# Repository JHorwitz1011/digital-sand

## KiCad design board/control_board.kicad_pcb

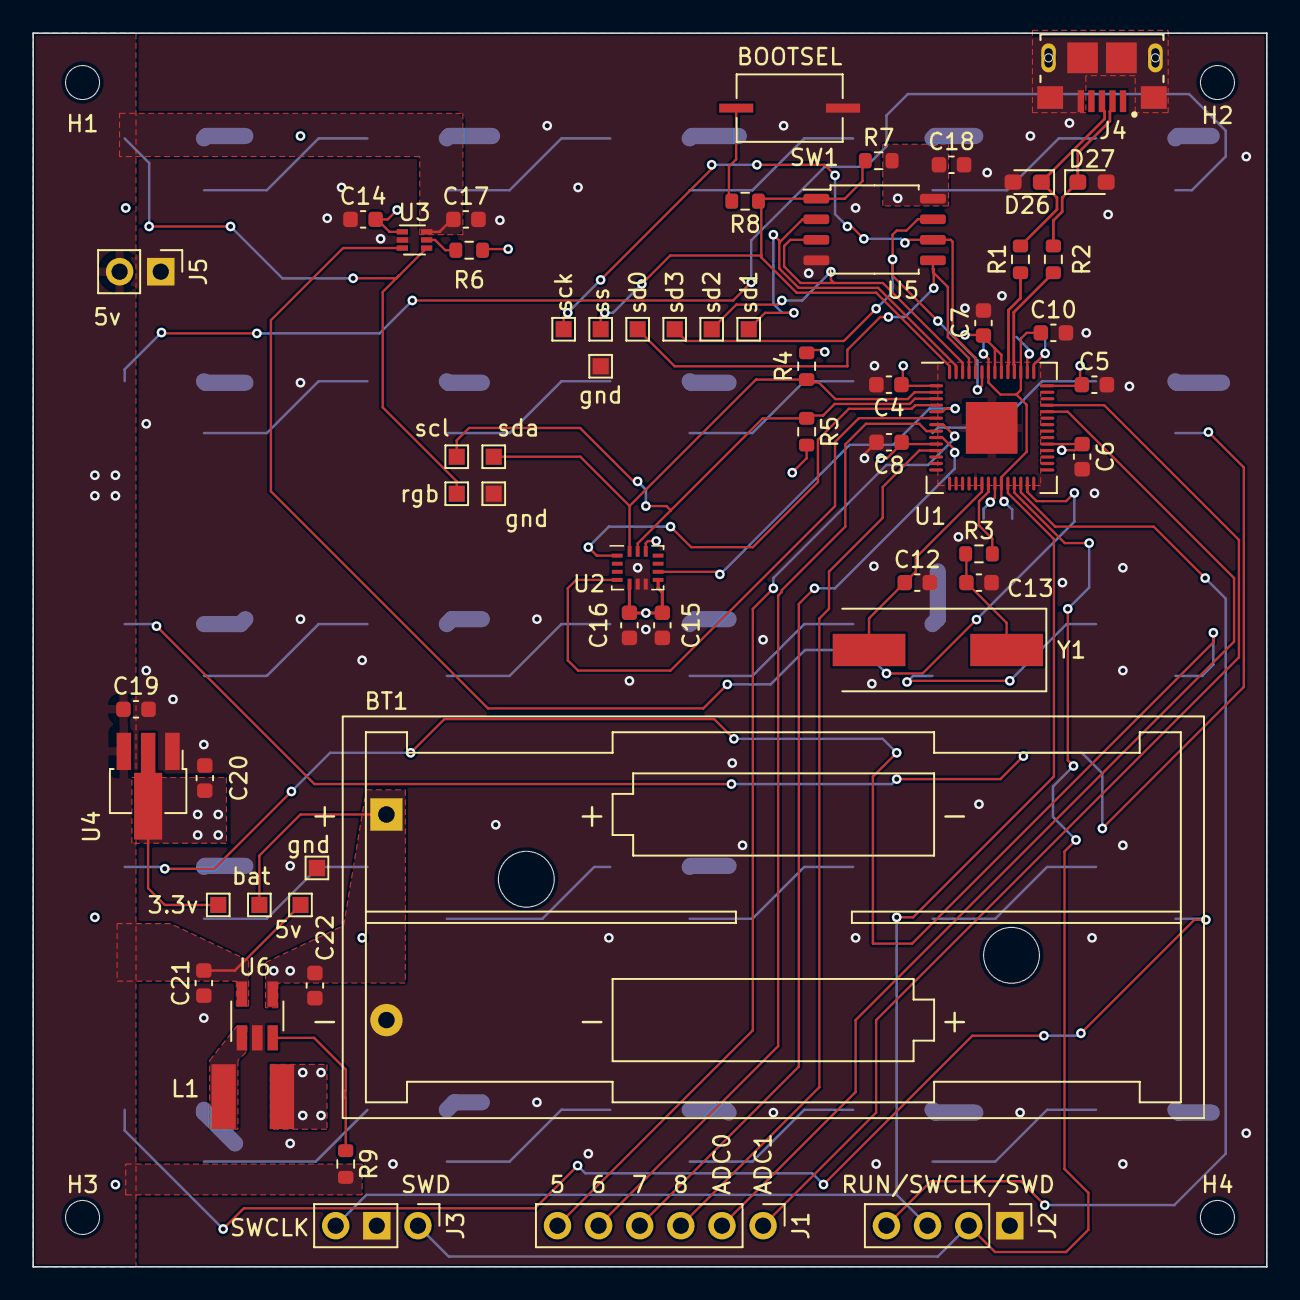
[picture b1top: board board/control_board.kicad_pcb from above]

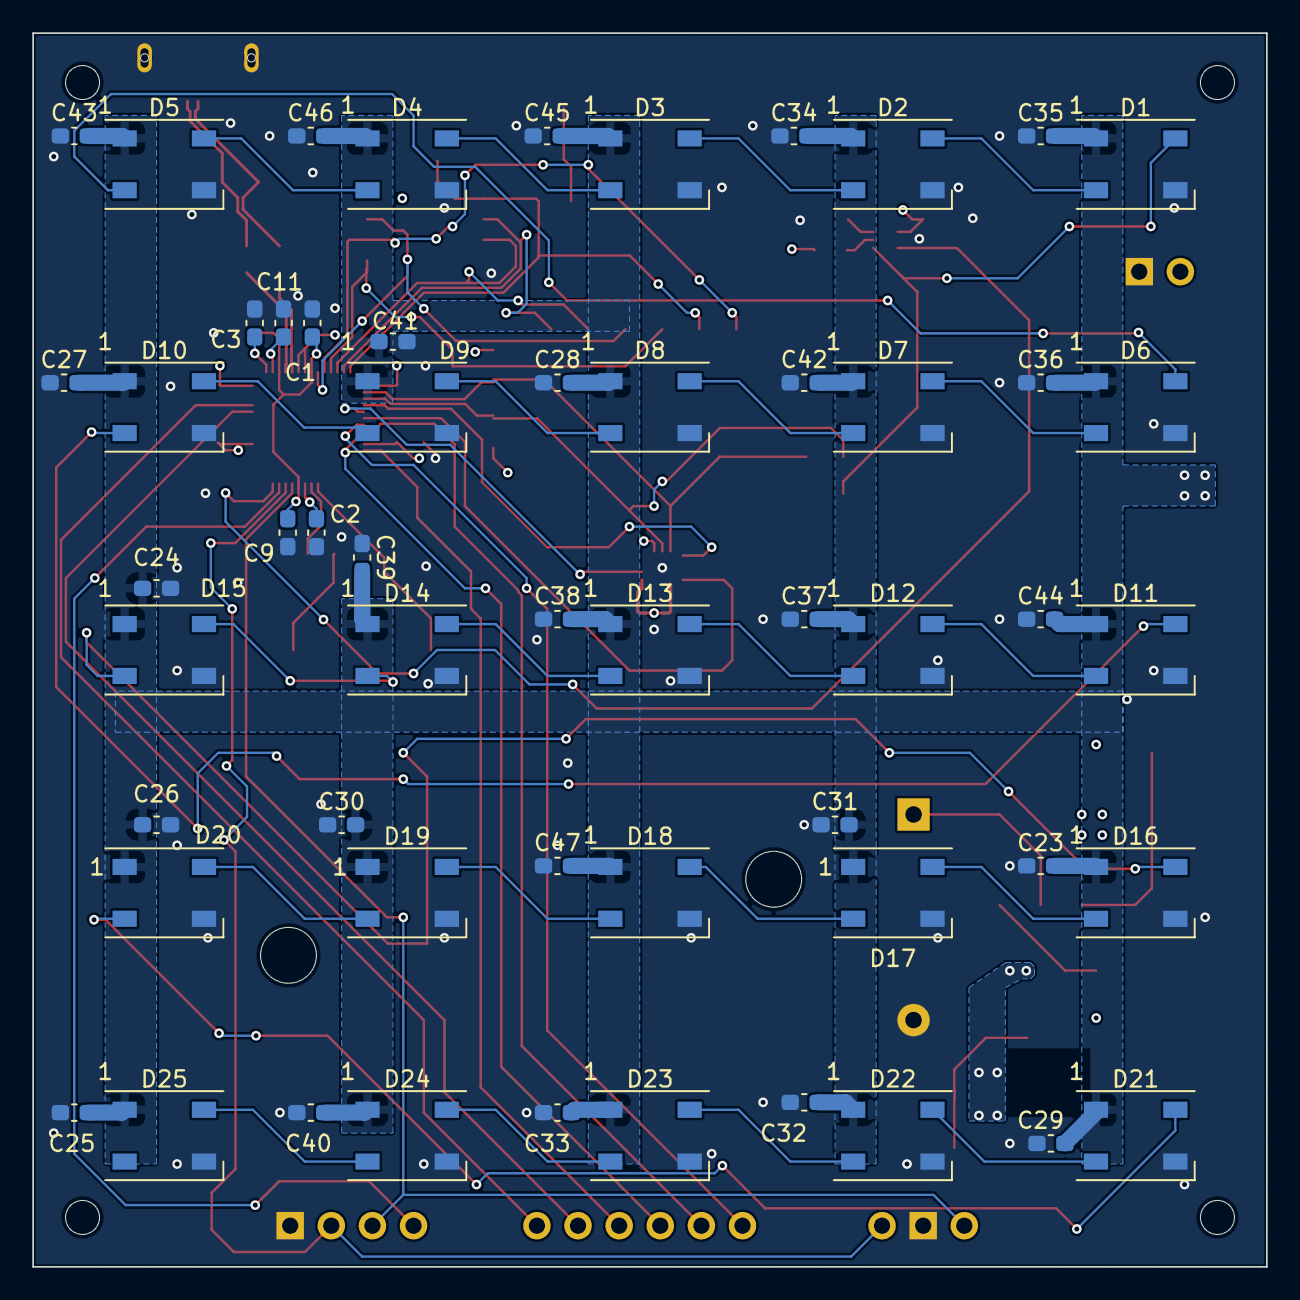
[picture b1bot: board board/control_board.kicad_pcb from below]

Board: 4 copper layers, 76.2 x 76.2 mm, 117 parts (55 on the bottom side), 62 nets.

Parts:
3.3v, 5v: TestPoint; TestPoint_Pad_1.0x1.0mm
BT1: PRT13851; BatteryHolder_Keystone_2468_2xAAA
C1, C2, C3, C9: 100n; C_0603_1608Metric_Pad1.08x0.95mm_HandSolder
C4, C5, C6, C7, C8: 100n; C_0603_1608Metric
C10: 1u; C_0603_1608Metric
C11: 1u; C_0603_1608Metric_Pad1.08x0.95mm_HandSolder
C12, C13: 27p; C_0603_1608Metric
C14, C17: 0.1u; C_0603_1608Metric
C15, C16: 100nF; C_0603_1608Metric
C18, C19, C20: 10u; C_0603_1608Metric
C21, C22: 10uF; C_0603_1608Metric
C23, C24, C25, C26, C27, C28, C29, C30, C31, C32, C33, C34, C35, C36, C37, C38, C39, C40, C41, C42, C43, C44, C45, C46, C47: .1uF; C_0603_1608Metric_Pad1.08x0.95mm_HandSolder
D1, D2, D3, D4, D5, D6, D7, D8, D9, D10, D11, D12, D13, D14, D15, D16, D17, D18, D19, D20, D21, D22, D23, D24, D25: WS2812B; LED_WS2812B_PLCC4_5.0x5.0mm_P3.2mm
D26, D27: D; D_0603_1608Metric_Pad1.05x0.95mm_HandSolder
H1, H2, H3, H4: MountingHole; MountingHole_2.1mm
J1: Conn_01x06; PinHeader_1x06_P2.54mm_Vertical
J2: Conn_01x04; PinHeader_1x04_P2.54mm_Vertical
J3: SWD; PinHeader_1x03_P2.54mm_Vertical
J4: USB_B_Micro; Amphenol_MicroB_10118193
J5: Conn_01x02; PinHeader_1x02_P2.54mm_Vertical
L1: 2.2uH; Inductor_NRS5024T2R2NMGJ
R1, R2: 27.4; R_0603_1608Metric
R3, R8: 1k; R_0603_1608Metric
R4, R5, R6, R7, R9: 10k; R_0603_1608Metric
SW1: BOOTSEL; PTS636 6.0x3.5 Button
U1: RP2040; QFN-56_EP_7.75x7.75_Pitch0.4mm
U2: BMI270; Bosch_LGA-14_3x2.5mm_P0.5mm
U3: SN74LVC1T45DRL; SOT-563
U4: AZ1117-3.3; SOT-89-3_Handsoldering
U5: W25Q128JVS; SOIC-8_5.23x5.23mm_P1.27mm
U6: RP402N; SOT-23-5_HandSoldering
Y1: Crystal; Crystal_SMD_HC49-SD
bat: TestPoint; TestPoint_Pad_1.0x1.0mm
gnd: TestPoint; TestPoint_Pad_1.0x1.0mm
gnd#2, gnd#3: TestPoint; TestPoint_Pad_1.0x1.0mm
rgb: TestPoint; TestPoint_Pad_1.0x1.0mm
sck: TestPoint; TestPoint_Pad_1.0x1.0mm
scl: TestPoint; TestPoint_Pad_1.0x1.0mm
sd0, sd1, sd2, sd3: TestPoint; TestPoint_Pad_1.0x1.0mm
sda: TestPoint; TestPoint_Pad_1.0x1.0mm
ss: TestPoint; TestPoint_Pad_1.0x1.0mm

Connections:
+1V1: C1.1, C2.1, C10.1, U1.23 (DVDD), U1.45 (VREG_VOUT), U1.50 (DVDD)
+3V3: 3.3v.1, C3.1, C4.1, C5.1, C6.1, C7.1, C8.1, C9.1, C11.1, C14.2, C15.2, C16.1, C18.1, C20.1, R4.2, R5.2, R6.2, R7.2, U1.1 (IOVDD), U1.10 (IOVDD), U1.22 (IOVDD), U1.33 (IOVDD), U1.42 (IOVDD), U1.43 (ADC_IOVDD), U1.44 (VREG_IOVDD), U1.48 (USB_IOVDD), U1.49 (IOVDD), U2.5 (VDDIO), U2.8 (VDD), U2.12 (CSB), U3.1 (VCCA), U4.2 (VO), U5.8 (VCC)
+5V: 5v.1, C17.1, C19.1, C21.2, C23.2, C24.2, C25.2, C26.2, C27.2, C28.2, C29.2, C30.2, C31.2, C32.2, C33.2, C34.2, C35.2, C36.2, C37.2, C38.2, C39.2, C40.2, C41.2, C42.2, C43.2, C44.2, C45.2, C46.2, C47.2, D1.1 (VDD), D2.1 (VDD), D3.1 (VDD), D4.1 (VDD), D5.1 (VDD), D6.1 (VDD), D7.1 (VDD), D8.1 (VDD), D9.1 (VDD), D10.1 (VDD), D11.1 (VDD), D12.1 (VDD), D13.1 (VDD), D14.1 (VDD), D15.1 (VDD), D16.1 (VDD), D17.1 (VDD), D18.1 (VDD), D19.1 (VDD), D20.1 (VDD), D21.1 (VDD), D22.1 (VDD), D23.1 (VDD), D24.1 (VDD), D25.1 (VDD), J5.2, R9.2, U3.6 (VCCB), U4.3 (VI), U6.5 (VOUT)
+BATT: BT1.1 (+), C22.2, L1.1, U6.4 (VIN), bat.1
/ADC0: J1.2, U1.38 (GPIO26_ADC0)
/ADC1: J1.1, U1.39 (GPIO27_ADC1)
/CRYSTAL_OUT: C13.1, R3.1, Y1.1
/GPIO5: J1.6, U1.7 (GPIO5)
/GPIO6: J1.5, U1.8 (GPIO6)
/GPIO7: J1.4, U1.9 (GPIO7)
/GPIO8: J1.3, U1.11 (GPIO8)
/IMU INT1: U1.6 (GPIO4), U2.4 (INT1)
/IMU INT2: U1.5 (GPIO3), U2.9 (INT2)
/Lx: L1.2, U6.1 (Lx)
/NEOPIX: U1.27 (GPIO16), U3.3 (A)
/QSPI_SCLK: U1.52 (QSPI_SCLK), U5.6 (CLK), sck.1
/QSPI_SD0: U1.53 (QSPI_SD0), U5.5 (DI(IO0)), sd0.1
/QSPI_SD1: U1.55 (QSPI_SD1), U5.2 (DO(IO1)), sd1.1
/QSPI_SD2: U1.54 (QSPI_SD2), U5.3 (IO2), sd2.1
/QSPI_SD3: U1.51 (QSPI_SD3), U5.7 (IO3), sd3.1
/QSPI_SS: R7.1, R8.1, U1.56 (QSPI_SS), U5.1 (~CS), ss.1
/RGB_DIN: D1.4 (DIN), U3.4 (B), rgb.1
/RPN: R2.1, U1.46 (USB_DM)
/RPP: R1.1, U1.47 (USB_DP)
/RUN: J2.4, U1.26 (RUN)
/SA0: U1.4 (GPIO2), U2.1 (SDO)
/SCL: R5.1, U1.3 (GPIO1), U2.13 (SCx), scl.1
/SDA: R4.1, U1.2 (GPIO0), U2.14 (SDx), sda.1
/SWCLK: J2.3, J3.3, U1.24 (SWCLK)
/SWD: J2.2, J3.1, U1.25 (SWD)
/USB_BOOT: R8.2, SW1.2
/USB_DN: D27.1 (K), J4.2 (D-), R2.2
/USB_DP: D26.1 (K), J4.3 (D+), R1.2
/XIN: C12.1, U1.20 (XIN), Y1.2
/XOUT: R3.2, U1.21 (XOUT)
GND: BT1.2 (-), C1.2, C2.2, C3.2, C4.2, C5.2, C6.2, C7.2, C8.2, C9.2, C10.2, C11.2, C12.2, C13.2, C14.1, C15.1, C16.2, C17.2, C18.2, C19.2, C20.2, C21.1, C22.1, C23.1, C24.1, C25.1, C26.1, C27.1, C28.1, C29.1, C30.1, C31.1, C32.1, C33.1, C34.1, C35.1, C36.1, C37.1, C38.1, C39.1, C40.1, C41.1, C42.1, C43.1, C44.1, C45.1, C46.1, C47.1, D1.3 (VSS), D2.3 (VSS), D3.3 (VSS), D4.3 (VSS), D5.3 (VSS), D6.3 (VSS), D7.3 (VSS), D8.3 (VSS), D9.3 (VSS), D10.3 (VSS), D11.3 (VSS), D12.3 (VSS), D13.3 (VSS), D14.3 (VSS), D15.3 (VSS), D16.3 (VSS), D17.3 (VSS), D18.3 (VSS), D19.3 (VSS), D20.3 (VSS), D21.3 (VSS), D22.3 (VSS), D23.3 (VSS), D24.3 (VSS), D25.3 (VSS), D26.2 (A), D27.2 (A), J2.1, J3.2, J4.5 (GND), J4.6 (Shield), J5.1, SW1.1, U1.19 (TESTEN), U1.57 (GND), U2.6 (GNDIO), U2.7 (GND), U3.2 (GND), U4.1 (GND), U5.4 (GND), U6.2 (GND), gnd.1, gnd#2.1, gnd#3.1
unnamed: D1.2 (DOUT), D2.4 (DIN)
unnamed: D2.2 (DOUT), D3.4 (DIN)
unnamed: D3.2 (DOUT), D4.4 (DIN)
unnamed: D4.2 (DOUT), D5.4 (DIN)
unnamed: D5.2 (DOUT), D6.4 (DIN)
unnamed: D6.2 (DOUT), D7.4 (DIN)
unnamed: D7.2 (DOUT), D8.4 (DIN)
unnamed: D8.2 (DOUT), D9.4 (DIN)
unnamed: D10.2 (DOUT), D11.4 (DIN)
unnamed: D9.2 (DOUT), D10.4 (DIN)
unnamed: D11.2 (DOUT), D12.4 (DIN)
unnamed: D12.2 (DOUT), D13.4 (DIN)
unnamed: D13.2 (DOUT), D14.4 (DIN)
unnamed: D14.2 (DOUT), D15.4 (DIN)
unnamed: D15.2 (DOUT), D16.4 (DIN)
unnamed: D16.2 (DOUT), D17.4 (DIN)
unnamed: D17.2 (DOUT), D18.4 (DIN)
unnamed: D18.2 (DOUT), D19.4 (DIN)
unnamed: D19.2 (DOUT), D20.4 (DIN)
unnamed: D20.2 (DOUT), D21.4 (DIN)
unnamed: D21.2 (DOUT), D22.4 (DIN)
unnamed: D22.2 (DOUT), D23.4 (DIN)
unnamed: D23.2 (DOUT), D24.4 (DIN)
unnamed: D24.2 (DOUT), D25.4 (DIN)
unnamed: R6.1, U3.5 (DIR)
unnamed: R9.1, U6.3 (EN)

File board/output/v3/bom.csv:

Comment,Designator,Footprint,LCSC Part #
100n Unpolarized capacitor,"C1,C2,C3,C9",C_0603_1608Metric_Pad1.08x0.95mm_HandSolder,
100n Unpolarized capacitor,"C4,C5,C6,C7,C8",C_0603_1608Metric,
1u Unpolarized capacitor,C10,C_0603_1608Metric,
1u Unpolarized capacitor,C11,C_0603_1608Metric_Pad1.08x0.95mm_HandSolder,
27p Unpolarized capacitor,"C12,C13",C_0603_1608Metric,
0.1u Unpolarized capacitor,"C14,C17",C_0603_1608Metric,
100nF Unpolarized capacitor,"C15,C16",C_0603_1608Metric,
10u Unpolarized capacitor,"C18,C19,C20",C_0603_1608Metric,
10uF Unpolarized capacitor,"C21,C22",C_0603_1608Metric,
.1uF Unpolarized capacitor,"C23,C24,C25,C26,C27,C28,C29,C30,C31,C32,C33,C34,C35,C36,C37,C38,C39,C40,C41,C42,C43,C44,C45,C46,C47",C_0603_1608Metric_Pad1.08x0.95mm_HandSolder,
WS2812B RGB LED with integrated controller,"D1,D2,D3,D4,D5,D6,D7,D8,D9,D10,D11,D12,D13,D14,D15,D16,D17,D18,D19,D20,D21,D22,D23,D24,D25",LED_WS2812B_PLCC4_5.0x5.0mm_P3.2mm,C2761795
D Diode,"D26,D27",D_0603_1608Metric_Pad1.05x0.95mm_HandSolder,C5224062
USB_B_Micro USB Micro Type B connector,J4,Amphenol_MicroB_10118193,C132562
2.2uH Inductor,L1,Inductor_NRS5024T2R2NMGJ,C222926
27.4 Resistor,"R1,R2",R_0603_1608Metric,
1k Resistor,"R3,R8",R_0603_1608Metric,
10k Resistor,"R4,R5,R6,R7,R9",R_0603_1608Metric,
"BOOTSEL 1x DIP Switch, Single Pole Single Throw (SPST) switch, small symbol",SW1,PTS636 6.0x3.5 Button,C2800965
RP2040 ,U1,QFN-56_EP_7.75x7.75_Pitch0.4mm,C2040
BMI270 ,U2,Bosch_LGA-14_3x2.5mm_P0.5mm,C2836813
"SN74LVC1T45DRL Single-Bit Dual-Supply Bus Transceiver With Configurable Voltage Translation and 3-State Outputs, SOT-563",U3,SOT-563,C352970
"AZ1117-3.3 1A 20V Fixed LDO Linear Regulator, 3.3V, SOT-89/SOT-223/TO-220/TO-252/TO-263",U4,SOT-89-3_Handsoldering,C460428
"W25Q128JVS 128Mb Serial Flash Memory, Standard/Dual/Quad SPI, SOIC-8",U5,SOIC-8_5.23x5.23mm_P1.27mm,C2613930
Crystal Two pin crystal,Y1,Crystal_SMD_HC49-SD,C1985239

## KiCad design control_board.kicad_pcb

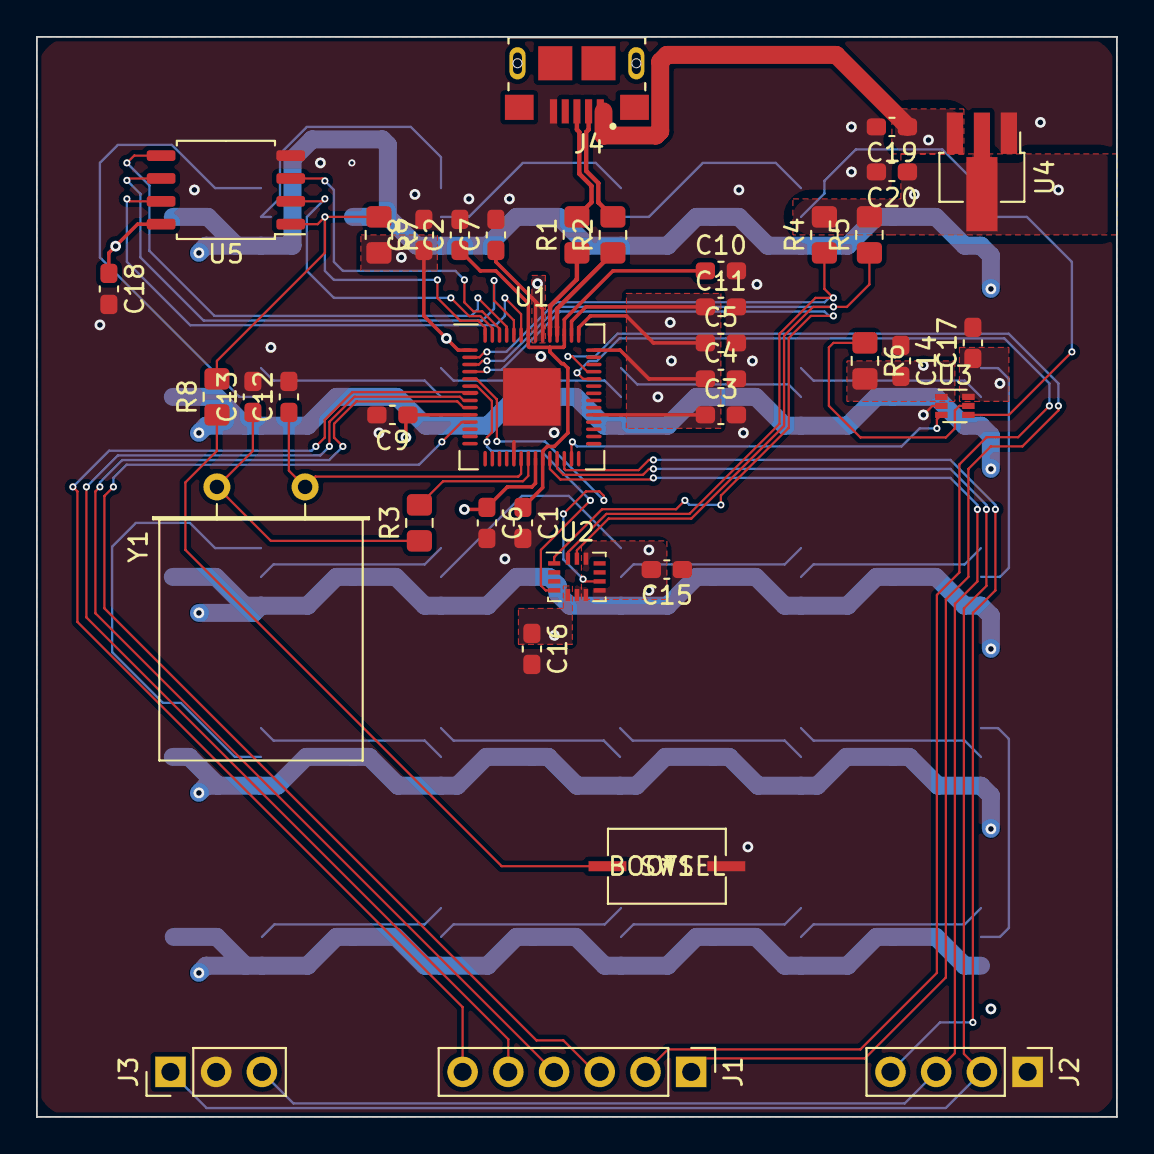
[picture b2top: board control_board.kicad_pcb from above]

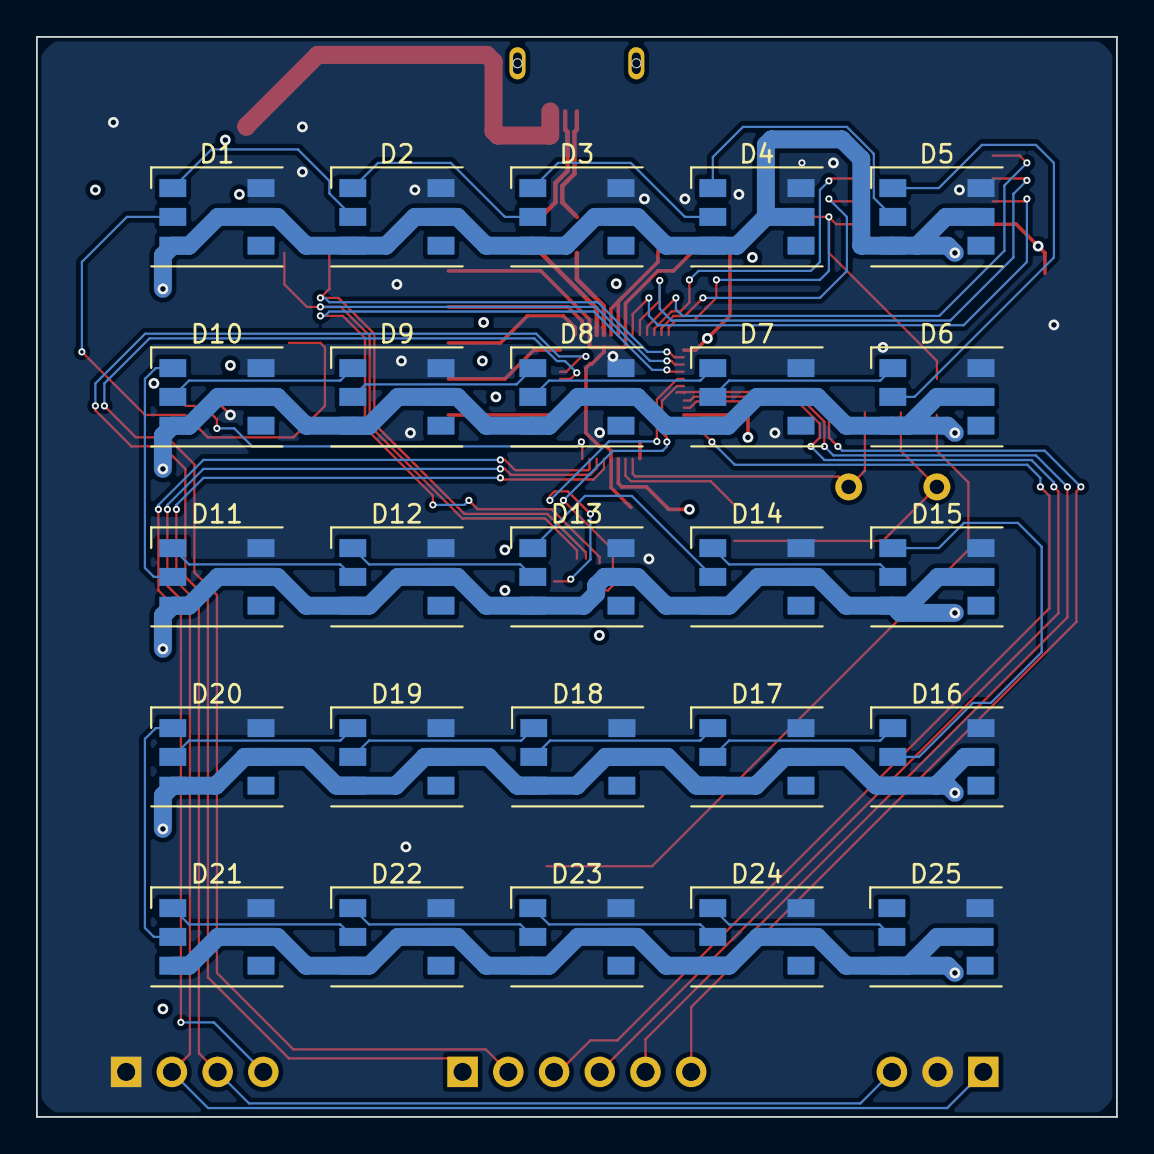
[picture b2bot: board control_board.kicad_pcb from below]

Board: 4 copper layers, 60.0 x 60.0 mm, 64 parts (25 on the bottom side), 59 nets.

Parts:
C1, C2, C3, C4, C5, C6, C7, C8, C9: 100n; C_0603_1608Metric_Pad1.08x0.95mm_HandSolder
C10, C11: 1u; C_0603_1608Metric_Pad1.08x0.95mm_HandSolder
C12, C13: 27p; C_0603_1608Metric_Pad1.08x0.95mm_HandSolder
C14, C17: 0.1u; C_0603_1608Metric_Pad1.08x0.95mm_HandSolder
C15, C16: 100nF; C_0603_1608Metric_Pad1.08x0.95mm_HandSolder
C18, C19, C20: 10u; C_0603_1608Metric_Pad1.08x0.95mm_HandSolder
D1, D2, D3, D4, D5, D6, D7, D8, D9, D10, D11, D12, D13, D14, D15, D16, D17, D18, D19, D20, D21, D22, D23, D24, D25: WS2812; LED_WS2812_PLCC6_5.0x5.0mm_P1.6mm
J1: Conn_01x06; PinHeader_1x06_P2.54mm_Vertical
J2: Conn_01x04; PinHeader_1x04_P2.54mm_Vertical
J3: SWD; PinHeader_1x03_P2.54mm_Vertical
J4: USB_B_Micro; Amphenol_MicroB_10118193
R1, R2: 27.4; R_0805_2012Metric_Pad1.20x1.40mm_HandSolder
R3, R8: 1k; R_0805_2012Metric_Pad1.20x1.40mm_HandSolder
R4, R5, R6, R7: 10k; R_0805_2012Metric_Pad1.20x1.40mm_HandSolder
SW1: BOOTSEL; PTS636 SM25F SMTR LFS
U1: RP2040; QFN-56_EP_7.75x7.75_Pitch0.4mm
U2: BMI270; Bosch_LGA-14_3x2.5mm_P0.5mm
U3: SN74LVC1T45DRL; SOT-563
U4: AZ1117-3.3; SOT-89-3_Handsoldering
U5: W25Q128JVS; SOIC-8_5.23x5.23mm_P1.27mm
Y1: Crystal; Crystal_HC49-U_Horizontal

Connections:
+1V1: C1.1, C2.1, C10.1, U1.23 (DVDD), U1.45 (VREG_VOUT), U1.50 (DVDD)
+3V3: C3.1, C4.1, C5.1, C6.1, C7.1, C8.1, C9.1, C11.1, C14.2, C15.2, C16.1, C18.1, C20.1, R4.2, R5.2, R6.2, R7.2, U1.1 (IOVDD), U1.10 (IOVDD), U1.22 (IOVDD), U1.33 (IOVDD), U1.42 (IOVDD), U1.43 (ADC_IOVDD), U1.44 (VREG_IOVDD), U1.48 (USB_IOVDD), U1.49 (IOVDD), U2.5 (VDDIO), U2.8 (VDD), U2.12 (CSB), U3.1 (VCCA), U4.2 (VO), U5.8 (VCC)
+5V: C17.1, C19.1, D1.3 (VCC), D1.5 (VDD), D2.3 (VCC), D2.5 (VDD), D3.3 (VCC), D3.5 (VDD), D4.3 (VCC), D4.5 (VDD), D5.3 (VCC), D5.5 (VDD), D6.3 (VCC), D6.5 (VDD), D7.3 (VCC), D7.5 (VDD), D8.3 (VCC), D8.5 (VDD), D9.3 (VCC), D9.5 (VDD), D10.3 (VCC), D10.5 (VDD), D11.3 (VCC), D11.5 (VDD), D12.3 (VCC), D12.5 (VDD), D13.3 (VCC), D13.5 (VDD), D14.3 (VCC), D14.5 (VDD), D15.3 (VCC), D15.5 (VDD), D16.3 (VCC), D16.5 (VDD), D17.3 (VCC), D17.5 (VDD), D18.3 (VCC), D18.5 (VDD), D19.3 (VCC), D19.5 (VDD), D20.3 (VCC), D20.5 (VDD), D21.3 (VCC), D21.5 (VDD), D22.3 (VCC), D22.5 (VDD), D23.3 (VCC), D23.5 (VDD), D24.3 (VCC), D24.5 (VDD), D25.3 (VCC), D25.5 (VDD), J4.1 (VBUS), U3.6 (VCCB), U4.3 (VI)
/ADC0: J1.2, U1.38 (GPIO26_ADC0)
/ADC1: J1.1, U1.39 (GPIO27_ADC1)
/GPIO5: J1.6, U1.7 (GPIO5)
/GPIO6: J1.5, U1.8 (GPIO6)
/GPIO7: J1.4, U1.9 (GPIO7)
/GPIO8: J1.3, U1.11 (GPIO8)
/IMU INT1: U1.6 (GPIO4), U2.4 (INT1)
/IMU INT2: U1.5 (GPIO3), U2.9 (INT2)
/NEOPIX: U1.27 (GPIO16), U3.3 (A)
/QSPI_SCLK: U1.52 (QSPI_SCLK), U5.6 (CLK)
/QSPI_SD0: U1.53 (QSPI_SD0), U5.5 (DI(IO0))
/QSPI_SD1: U1.55 (QSPI_SD1), U5.2 (DO(IO1))
/QSPI_SD2: U1.54 (QSPI_SD2), U5.3 (IO2)
/QSPI_SD3: U1.51 (QSPI_SD3), U5.7 (IO3)
/QSPI_SS: R7.1, R8.2, U1.56 (QSPI_SS), U5.1 (~CS)
/RGB_DIN: D1.2 (DIN), U3.4 (B)
/RPN: R2.1, U1.46 (USB_DM)
/RPP: R1.1, U1.47 (USB_DP)
/RUN: J2.4, U1.26 (RUN)
/SA0: U1.4 (GPIO2), U2.1 (SDO)
/SCL: R5.1, U1.3 (GPIO1), U2.13 (SCx)
/SDA: R4.1, U1.2 (GPIO0), U2.14 (SDx)
/SWCLK: J2.3, J3.3, U1.24 (SWCLK)
/SWD: J2.2, J3.1, U1.25 (SWD)
/USB_BOOT: R8.1, SW1.2
/USB_DN: J4.2 (D-), R2.2
/USB_DP: J4.3 (D+), R1.2
/XIN: C12.1, U1.20 (XIN), Y1.2
/XOUT: R3.2, U1.21 (XOUT)
GND: C1.2, C2.2, C3.2, C4.2, C5.2, C6.2, C7.2, C8.2, C9.2, C10.2, C11.2, C12.2, C13.2, C14.1, C15.1, C16.2, C17.2, C18.2, C19.2, C20.2, D1.6 (VSS), D2.6 (VSS), D3.6 (VSS), D4.6 (VSS), D5.6 (VSS), D6.6 (VSS), D7.6 (VSS), D8.6 (VSS), D9.6 (VSS), D10.6 (VSS), D11.6 (VSS), D12.6 (VSS), D13.6 (VSS), D14.6 (VSS), D15.6 (VSS), D16.6 (VSS), D17.6 (VSS), D18.6 (VSS), D19.6 (VSS), D20.6 (VSS), D21.6 (VSS), D22.6 (VSS), D23.6 (VSS), D24.6 (VSS), D25.6 (VSS), J2.1, J3.2, J4.5 (GND), SW1.1, U1.19 (TESTEN), U1.57 (GND), U2.6 (GNDIO), U2.7 (GND), U3.2 (GND), U4.1 (GND), U5.4 (GND)
unnamed: C13.1, R3.1, Y1.1
unnamed: D1.1 (DOUT), D2.2 (DIN)
unnamed: D2.1 (DOUT), D3.2 (DIN)
unnamed: D3.1 (DOUT), D4.2 (DIN)
unnamed: D4.1 (DOUT), D5.2 (DIN)
unnamed: D5.1 (DOUT), D6.2 (DIN)
unnamed: D6.1 (DOUT), D7.2 (DIN)
unnamed: D7.1 (DOUT), D8.2 (DIN)
unnamed: D8.1 (DOUT), D9.2 (DIN)
unnamed: D10.1 (DOUT), D11.2 (DIN)
unnamed: D9.1 (DOUT), D10.2 (DIN)
unnamed: D11.1 (DOUT), D12.2 (DIN)
unnamed: D12.1 (DOUT), D13.2 (DIN)
unnamed: D13.1 (DOUT), D14.2 (DIN)
unnamed: D14.1 (DOUT), D15.2 (DIN)
unnamed: D15.1 (DOUT), D16.2 (DIN)
unnamed: D16.1 (DOUT), D17.2 (DIN)
unnamed: D17.1 (DOUT), D18.2 (DIN)
unnamed: D18.1 (DOUT), D19.2 (DIN)
unnamed: D19.1 (DOUT), D20.2 (DIN)
unnamed: D20.1 (DOUT), D21.2 (DIN)
unnamed: D21.1 (DOUT), D22.2 (DIN)
unnamed: D22.1 (DOUT), D23.2 (DIN)
unnamed: D23.1 (DOUT), D24.2 (DIN)
unnamed: D24.1 (DOUT), D25.2 (DIN)
unnamed: R6.1, U3.5 (DIR)

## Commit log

2023-12-30 physics sim starting
2024-07-09 code added

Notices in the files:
parts and their libraries:
Copyright 2021 Accelerated Designs. All rights reserved.
